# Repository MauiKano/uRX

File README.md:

# uRX Navtex SDR – System Documentation

## 1. Overview
The **uRX** is a high-performance Software Defined Radio (SDR) receiver, specifically optimized for **Navtex** transmissions (518 kHz / 490 kHz). It combines the processing power of the **ESP32-S3** with a precision **Tayloe Mixer** and the versatility of the **Si4732** radio chip.

This project is licensed under the **GNU General Public License v3.0 (GPL-3.0)**.

---

## 2. Technical Hardware Specification

### RF Frontend & Antenna Management
*   **Resonant Ferrite Rod Antenna:** Tuned as a high-Q circuit for the target frequencies.
*   **Signal Splitting:** The antenna signal is buffered and isolated via an **OPA2211** operational amplifier.
*   **Parallel Architecture:** The OPA2211 output simultaneously feeds the **Tayloe Mixer (CBT3253)** for SDR decoding and the **AM antenna input of the Si4732** for parallel monitoring.
*   **ATS-Mini Heritage:** The tuner section for the Si4732 implements the proven circuit design of the **ATS-Mini**, including an optimized FM input network (180nH / 18pF).

### Signal Processing (SDR & Audio)
*   **Dual-Channel Digitization:** A **PCM1808 24-bit ADC** handles the conversion.
    *   **Channel 1 (I/Q SDR):** Differential I/Q signals from the Tayloe Mixer are amplified via an **LM4562** instrumentation stage.
    *   **Channel 2 (Si4732 Audio):** The analog audio output of the Si4732 is routed to the second ADC channel for digital post-processing.
*   **I2S Integration:** Data is streamed via I2S to the ESP32-S3 for real-time decoding and noise reduction.
*   **Audio Output:** A **PAM8406** power amplifier drives the speaker. A dedicated PDM/PWM output provides audio tones for Navtex monitoring.

### Dual Display Architecture
The uRX features a unique dual-display system for maximum utility:
*   **4.2" E-Ink Display:** For low-power, high-contrast viewing of decoded Navtex text messages.
*   **1.9" TFT Display:** For real-time tuning, spectrum visualization, and system menus.

---

## 3. ESP32-S3 GPIO Assignment (WROOM-2 N16)
*Note: Optimized for the N16 (non-PSRAM) variant to ensure all GPIOs are available for peripherals.*

| Function | GPIO | Module Pin | Details |
| :--- | :--- | :--- | :--- |
| **I2C SDA** | 18 | 11 | Si4732, Si5351 (4.7k Pull-up) |
| **I2C SCL** | 03 | 15 | Si4732, Si5351 (4.7k Pull-up) |
| **SPI MOSI** | 01 | 39 | Shared Data (MOSI) |
| **SPI SCLK** | 02 | 38 | Shared Clock (SCLK) |
| **E-INK CS** | 04 | 08 | E-Ink Chip Select |
| **E-INK DC** | 05 | 09 | E-Ink Data/Command |
| **E-INK RST** | 06 | 10 | E-Ink Reset |
| **TFT CS** | 42 | 33 | TFT Chip Select |
| **TFT DC** | 44 | 37 | TFT Data/Command |
| **TFT RST** | 43 | 36 | TFT Reset |
| **I2S_DATA** | 13 | 21 | From PCM1808 ADC |
| **I2S_BCK** | 12 | 20 | Bit Clock (ADC) |
| **I2S_WS** | 11 | 19 | Word Select (ADC) |
| **GPS TX** | 16 | 09 | Data from GPS |
| **GPS RX** | 17 | 10 | Data to GPS |
| **GPS Power** | 15 | 28 | Controls BC847 (GND-Switch) |
| **Audio Out** | 10 | 18 | PDM/PWM Navtex Tones |
| **Encoder A/B**| 38/39| 31/32 | Rotary Encoder Phases |
| **Encoder SW** | 40 | 33 | Encoder Push-Switch |

---

## 4. Installation & Setup
1.  **Environment:** [PlatformIO](https://platformio.org) is recommended.
2.  **Configuration:** Hardware pins are defined in `include/config.h`. 
3.  **Libraries:** GxEPD2, TFT_eSPI, PU2CLR Si4735, Etherkit Si5351, TinyGPS++.
4.  **Flash:** Ensure `ARDUINO_USB_CDC_ON_BOOT=1` is set in `platformio.ini` for native USB programming.

---

## 5. Power & Safety
The system is powered by a **2S LiPo battery (8.4V)** charged via USB-C using the **IP2326**. Ferrite beads and L-C star-filtering are used to protect the sensitive RF stages from switching noise.

**Disclaimer:** This is an experimental open-source project. Handle LiPo batteries with care.

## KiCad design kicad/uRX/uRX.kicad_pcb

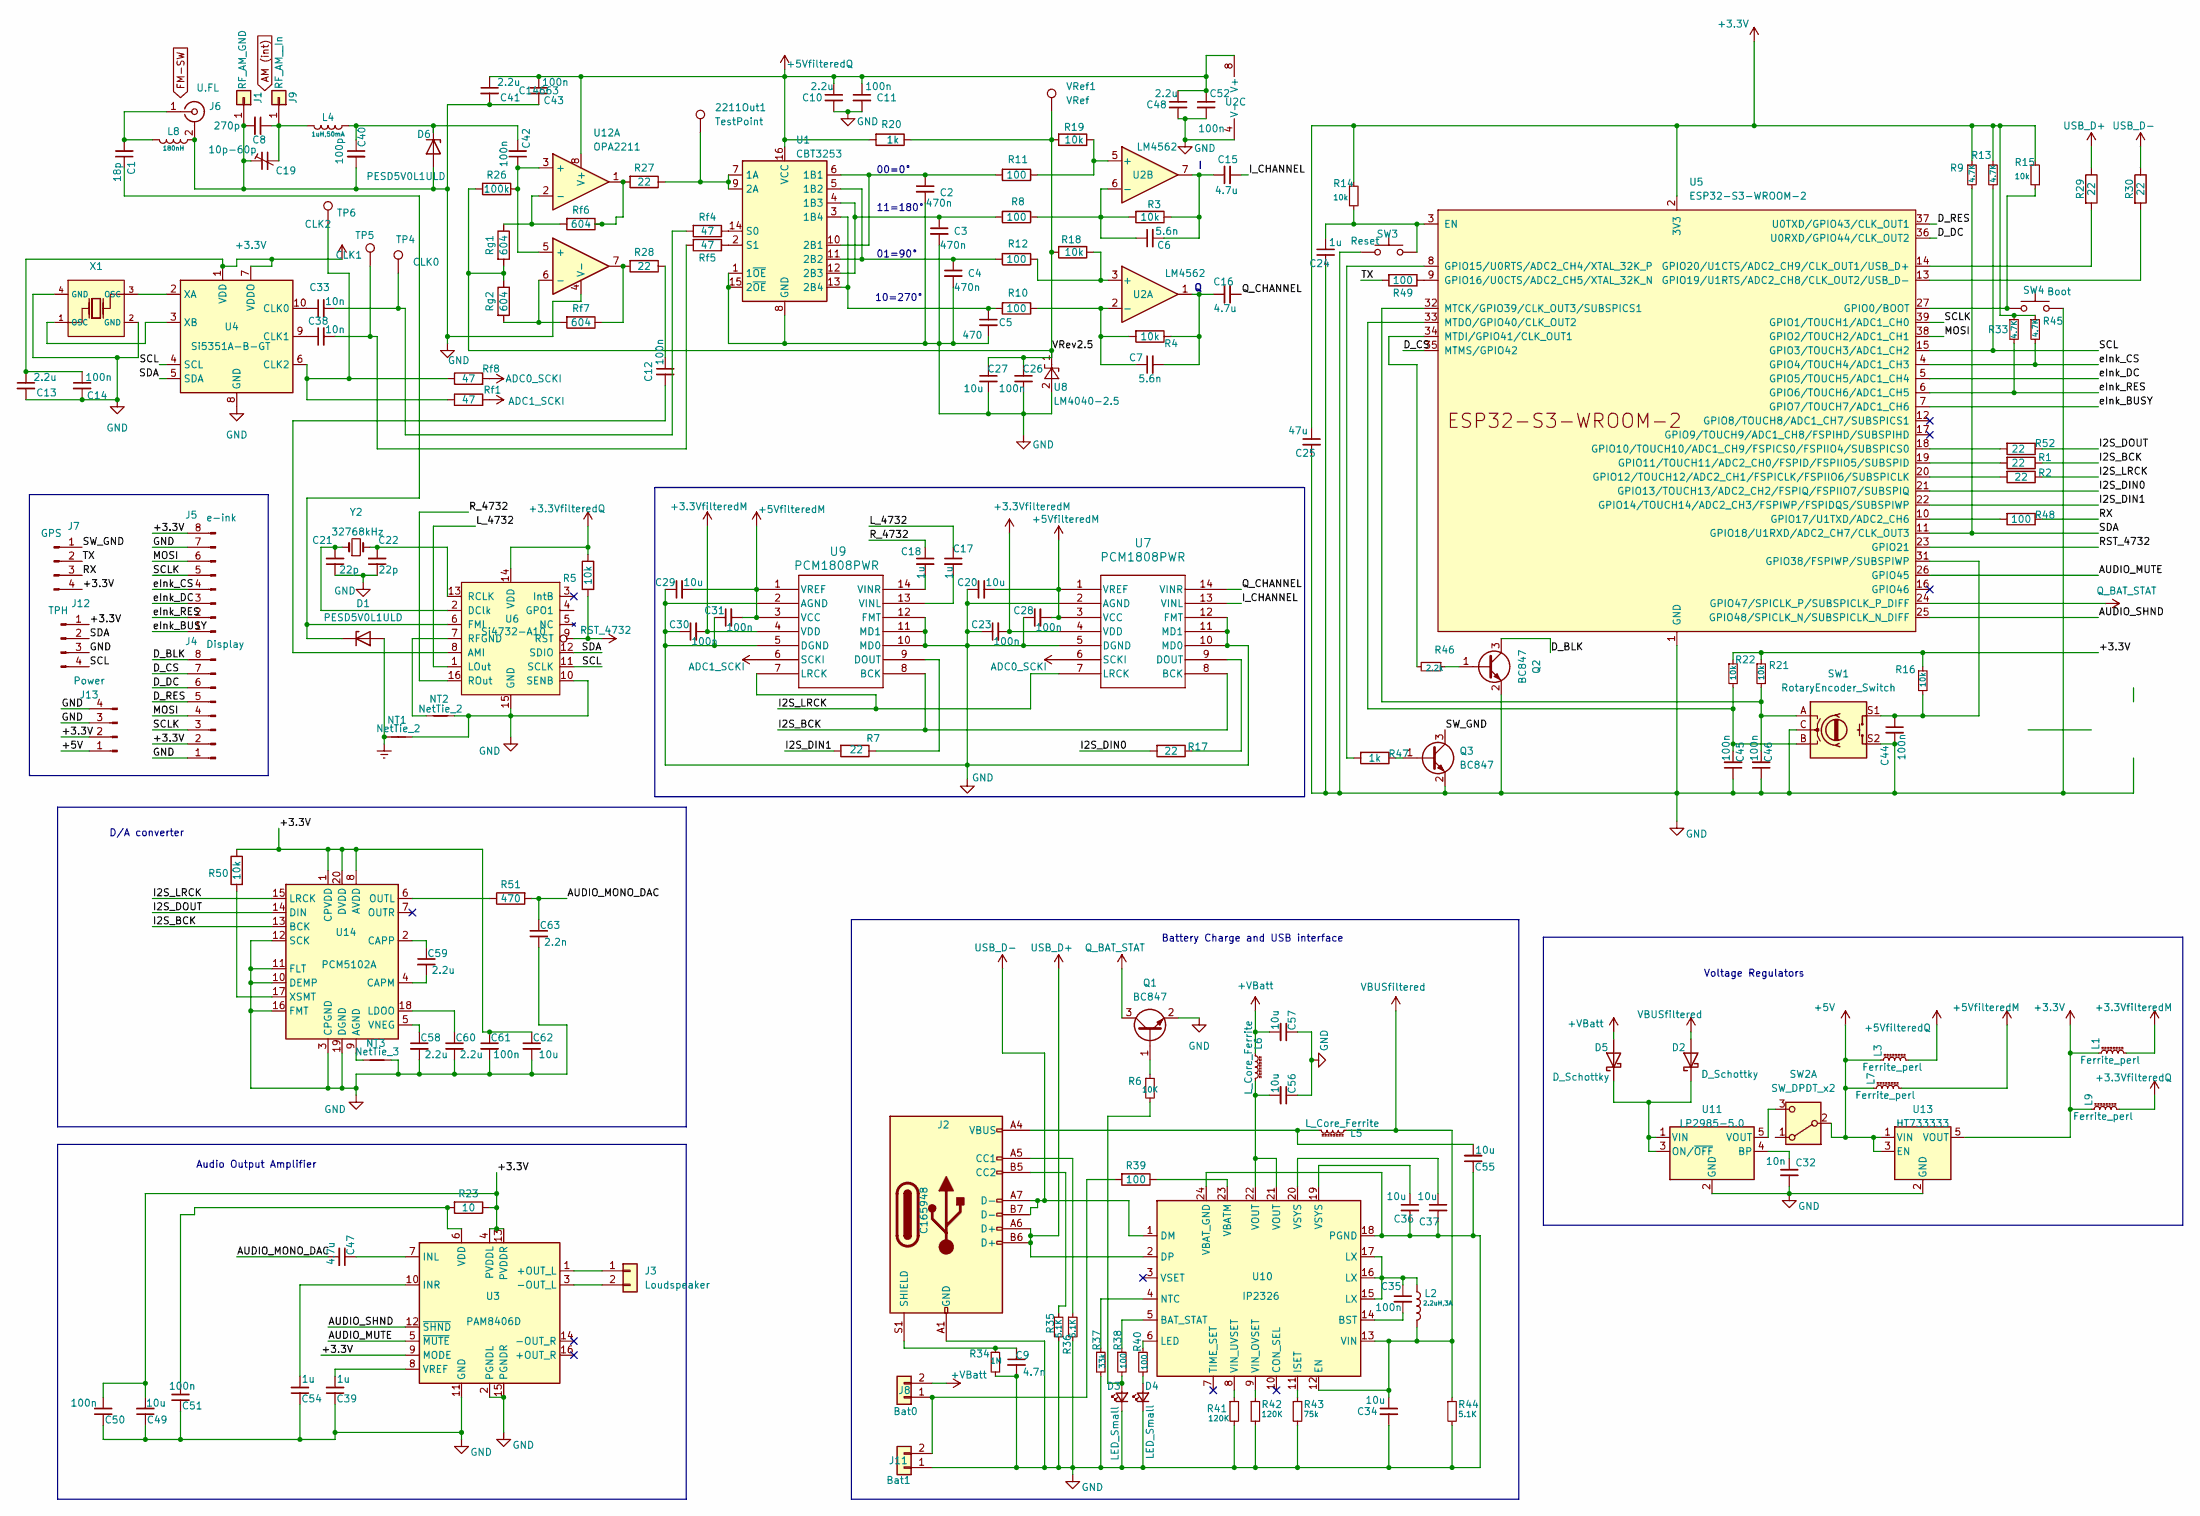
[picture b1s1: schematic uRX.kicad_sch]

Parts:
2211Out1: TestPoint; TestPoint_THTPad_1.0x1.0mm_Drill0.5mm
C1: 18p; C_0603_1608Metric
C2, C3, C4: 470n; C_0603_1608Metric
C5: 470; C_0603_1608Metric
C6, C7: 5.6n; C_0603_1608Metric
C8: 270p; C_0603_1608Metric
C9: 4.7n; C_0603_1608Metric
C10, C13, C41, C48, C58, C59, C60: 2.2u; C_0603_1608Metric
C11, C12, C14, C23, C26, C28, C30, C31, C35, C42, C43, C44, C45, C46, C50, C51, C52, C61: 100n; C_0603_1608Metric
C15, C16, C47: 4.7u; C_0603_1608Metric
C17, C18, C24, C39, C54: 1u; C_0603_1608Metric
C19: 10p-60p; C_Trimmer_Murata_TZC3
C20, C27, C29, C36, C37, C49, C62: 10u; C_0603_1608Metric
C21, C22: 22p; C_0603_1608Metric
C25: 47u; C_0603_1608Metric
C32, C33, C38: 10n; C_0603_1608Metric
C34, C55, C56, C57: 10u; C_0805_2012Metric
C40: 100p; C_0603_1608Metric
C63: 2.2n; C_0603_1608Metric
D1, D6: PESD5V0L1ULD; D_SOD-882D
D2, D5: D_Schottky; D_SOD-123
D3, D4: LED_Small; LED_0603_1608Metric
J1: RF_AM_GND; Pin_D0.9mm_L10.0mm_W2.4mm_FlatFork
J2: C165948; USB_C_Receptacle_GCT_USB4085
J3: Loudspeaker; JST_PH_B2B-PH-K_1x02_P2.00mm_Vertical
J4: Display; PinHeader_1x08_P2.54mm_Vertical
J5: e-ink; PinHeader_1x08_P1.27mm_Horizontal
J6: U.FL; SMA_Molex_73251-1153_EdgeMount_Horizontal; LCSC C5137195
J7: GPS; PinHeader_1x04_P2.54mm_Vertical
J8: Bat0; JST_PH_B2B-PH-K_1x02_P2.00mm_Vertical
J9: RF_AM__In; Pin_D0.9mm_L10.0mm_W2.4mm_FlatFork
J11: Bat1; JST_PH_B2B-PH-K_1x02_P2.00mm_Vertical
J12: TPH; PinHeader_1x04_P2.54mm_Vertical
J13: Power; PinHeader_1x04_P2.54mm_Vertical
L1, L3, L7, L9: Ferrite_perl; L_0603_1608Metric
L2: 2.2uH,3A; L_Taiyo-Yuden_NR-40xx; Tolerance ±10%; Part NRS5024T2R2NMGJ; LCSC C222926
L4: 1uH,50mA; L_0805; Tolerance ±10%; Part SDFL2012Q1R0KTF; LCSC C1042
L5, L6: L_Core_Ferrite; L_Taiyo-Yuden_NR-40xx
L8: 180nH; L_0805; Tolerance ±10%; Part SDFL2012Q1R0KTF; LCSC C1042
NT1, NT2: NetTie_2; NetTie-2_SMD_Pad0.5mm
NT3: NetTie_3; NetTie-2_SMD_Pad0.5mm
Q1, Q2, Q3: BC847; SOT-23
R1, R2, R7, R17, R27, R28, R29, R30, R52: 22; R_0603_1608Metric
R3, R4, R5, R14, R15, R16, R18, R19, R21, R22, R50: 10k; R_0603_1608Metric
R6: 10K; R_0603_1608Metric
R8, R10, R11, R12, R38, R39, R40, R48, R49: 100; R_0603_1608Metric
R9, R13, R33, R45: 4.7K; R_0603_1608Metric
R20, R47: 1k; R_0603_1608Metric
R23: 10; R_0603_1608Metric
R26: 100k; R_0603_1608Metric
R34: 1M; R_0603_1608Metric
R35, R36, R44: 5.1K; R_0603_1608Metric
R37: 33k; R_0603_1608Metric
R41, R42: 120K; R_0603_1608Metric
R43: 75k; R_0603_1608Metric
R46: 2.2k; R_0603_1608Metric
R51: 470; R_0603_1608Metric
Rf1, Rf4, Rf5, Rf8: 47; R_0603_1608Metric
Rf6, Rf7: 604; R_0603_1608Metric
Rg1, Rg2: 604; R_0603_1608Metric
SW1: RotaryEncoder_Switch; RotaryEncoder_Alps_EC11E-Switch_Vertical_H20mm
SW2: SW_DPDT_x2; SW_SPDT_PCM12
SW3: Reset; SW_SPST_B3U-1000P
SW4: Boot; SW_SPST_B3U-1000P
TP4: CLK0; TestPoint_THTPad_1.0x1.0mm_Drill0.5mm
TP5: CLK1; TestPoint_THTPad_1.0x1.0mm_Drill0.5mm
TP6: CLK2; TestPoint_THTPad_1.0x1.0mm_Drill0.5mm
U1: CBT3253; SO-16_3.9x9.9mm_P1.27mm
U2: LM4562; SOIC-8_3.9x4.9mm_P1.27mm
U3: PAM8406D; SOIC-16_3.9x9.9mm_P1.27mm
U4: Si5351A-B-GT; MSOP-10_3x3mm_P0.5mm
U5: ESP32-S3-WROOM-2
U6: Si4732-A10; SSOP-16_3.9x4.9mm_P0.635mm
U7, U9: PCM1808PWR; TSSOP-14_4.4x5mm_P0.65mm
U8: LM4040-2.5; SOT-23-3
U10: IP2326; QFN-24-1EP_4x4mm_P0.5mm_EP2.7x2.7mm
U11: LP2985-5.0; SOT-23-5
U12: OPA2211; SOIC-8_3.9x4.9mm_P1.27mm
U13: HT733333; SOT-23-5
U14: PCM5102A; TSSOP-20_4.4x6.5mm_P0.65mm
VRef1: VRef; TestPoint_THTPad_1.0x1.0mm_Drill0.5mm
X1: X322525MOB4SI; Crystal_SMD_3225-4Pin_3.2x2.5mm; Frequency Tolerance ±10ppm; Part X322525MOB4SI; LCSC C9006
Y2: 32768kHz; Crystal_SMD_3215-2Pin_3.2x1.5mm

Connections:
+3.3V: C13.1, C14.1, C25.1, C49.2, C50.2, C61.1, C62.1, J4.2, J5.8, J7.4, J12.1, J13.2, L1.1, L9.1, R9.1, R13.1, R14.1, R15.1, R16.1, R21.1, R22.1, R23.1, R33.1, R45.1, R50.1, U3.4 (PVDDL), U3.9 (MODE), U3.13 (PVDDR), U4.1 (VDD), U4.7 (VDDO), U5.2 (3V3), U13.5 (VOUT), U14.1 (CPVDD), U14.8 (AVDD), U14.20 (DVDD)
+3.3VfilteredM: C23.2, C30.2, L1.2, U7.4 (VDD), U9.4 (VDD)
+3.3VfilteredQ: L9.2, R5.1, U6.14 (VDD)
+5V: J13.1, L3.1, L7.1, SW2.2 (B), U13.1 (VIN), U13.3 (EN)
+5VfilteredM: C20.2, C28.2, C29.2, C31.2, L7.2, U7.1 (VREF), U7.3 (VCC), U9.1 (VREF), U9.3 (VCC)
+5VfilteredQ: C10.1, C11.1, C41.1, C43.1, C48.1, C52.1, L3.2, R20.2, U1.16 (VCC), U2.8 (V+), U12.8 (V+)
+VBatt: C57.2, D5.2 (A), J8.2, L6.1
/AUDIO_MONO_DAC: C47.2, C63.1, R51.2
/AUDIO_MUTE: U3.5 (~MUTE), U5.26 (GPIO45)
/AUDIO_SHND: U3.12 (~SHND), U5.25 (GPIO48/SPICLK_N/SUBSPICLK_N_DIFF)
/D_BLK: J4.8, Q2.3 (C)
/D_CS: J4.7, U5.35 (MTMS/GPIO42)
/D_DC: J4.6, U5.36 (U0RXD/GPIO44/CLK_OUT2)
/D_RES: J4.5, U5.37 (U0TXD/GPIO43/CLK_OUT1)
/I2S_BCK: R1.1, U7.8 (BCK), U9.8 (BCK), U14.13 (BCK)
/I2S_DIN0: R17.2, U5.21 (GPIO13/TOUCH13/ADC2_CH2/FSPIQ/FSPIIO7/S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)
/I2S_DIN1: R7.2, U5.22 (GPIO14/TOUCH14/ADC2_CH3/FSPIWP/FSPIDQS/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)
/I2S_DOUT: R52.1, U14.14 (DIN)
/I2S_LRCK: R2.1, U7.7 (LRCK), U9.7 (LRCK), U14.15 (LRCK)
/I_CHANNEL: C15.2, U7.13 (VINL)
/L_4732: C17.1, U6.1 (LOut)
/MOSI: J4.4, J5.6, U5.38 (GPIO2/TOUCH2/ADC1_CH1)
/Q_CHANNEL: C16.2, U7.14 (VINR)
/RX: J7.3, R48.1
/R_4732: C18.1, U6.16 (ROut)
/SCL: J12.4, R13.2, U4.4 (SCL), U5.15 (GPIO3/TOUCH3/ADC1_CH2), U6.11 (SCLK)
/SCLK: J4.3, J5.5, U5.39 (GPIO1/TOUCH1/ADC1_CH0)
/SDA: J12.2, R9.2, U4.5 (SDA), U5.11 (GPIO18/U1RXD/ADC2_CH7/CLK_OUT3), U6.12 (SDIO)
/SW_GND: J7.1, Q3.3 (C)
/TX: J7.2, R49.2
/VRev2.5: C26.1, C27.1, R18.2, R19.2, R20.1, R26.2, Rg1.2, Rg2.1, U8.1 (K), VRef1.1
/eInk_BUSY: J5.1, U5.7 (GPIO7/TOUCH7/ADC1_CH6)
/eInk_CS: J5.4, R45.2, U5.4 (GPIO4/TOUCH4/ADC1_CH3)
/eInk_DC: J5.3, U5.5 (GPIO5/TOUCH5/ADC1_CH4)
/eInk_RES: J5.2, R33.2, U5.6 (GPIO6/TOUCH6/ADC1_CH5)
ADC0_SCKI: Rf8.2, U7.6 (SCKI)
ADC1_SCKI: Rf1.2, U9.6 (SCKI)
Earth: D1.2 (A), NT1.1
unnamed: C12.1, R28.1
unnamed: C6.2, C15.1, R3.1, U2.7
unnamed: C7.2, C16.1, R4.1, U2.1
unnamed: C33.2, Rf4.2, TP4.1
unnamed: C35.1, L2.1, U10.15 (LX), U10.16 (LX), U10.17 (LX)
unnamed: C36.1, U10.19 (VSYS)
unnamed: C37.1, U10.20 (VSYS)
unnamed: C38.2, Rf5.2, TP5.1
unnamed: C42.1, R26.1, U12.3 (+), U12.5 (+)
unnamed: C55.2, J2.A4 (VBUS), J2.A9 (VBUS), J2.B4 (VBUS), J2.B9 (VBUS), L5.2
unnamed: C56.2, L6.2, U10.21 (VOUT), U10.22 (VOUT)
unnamed: C1.1, D1.1 (K), U6.6 (FMI)
unnamed: D2.1 (K), D5.1 (K), U11.1 (VIN), U11.3 (ON/~OFF)
unnamed: D3.2 (A), R6.2, R38.2
unnamed: D4.2 (A), R40.2
unnamed: C40.1, C42.2, D6.1 (K), L4.1
unnamed: J2.A5 (CC1), R36.1
unnamed: J2.B5 (CC2), R35.1
unnamed: C9.1, J2.S1 (SHIELD), R34.1
unnamed: J3.1, U3.1 (+OUT_L)
unnamed: J3.2, U3.3 (-OUT_L)
unnamed: C1.2, J6.1 (In), L8.2
unnamed: C8.1, C19.2, J9.1, L4.2
unnamed: J8.1, J11.2, R39.2
unnamed: Q1.1 (B), R6.1
unnamed: Q2.1 (B), R46.1
unnamed: Q3.1 (B), R47.1
unnamed: R27.2, Rf6.1, U12.1
unnamed: R28.2, Rf7.1, U12.7
unnamed: Rf6.2, Rg1.1, U12.2 (-)
unnamed: Rf7.2, Rg2.2, U12.6 (-)
unnamed: SW2.3 (C), U11.5 (VOUT)
unnamed: 2211Out1.1, R27.1, U1.7 (1A), U1.9 (2A)
unnamed: C2.1, R11.2, U1.6 (1B1), U1.10 (2B1)
unnamed: C4.1, R12.2, U1.5 (1B2), U1.11 (2B2)
unnamed: C3.1, R8.2, U1.4 (1B3), U1.12 (2B3)
unnamed: C5.1, R10.2, U1.3 (1B4), U1.13 (2B4)
unnamed: Rf4.1, U1.14 (S0)
unnamed: Rf5.1, U1.2 (S1)
unnamed: R12.1, R18.1, U2.3 (+)
unnamed: C7.1, R4.2, R10.1, U2.2 (-)
unnamed: R11.1, R19.1, U2.5 (+)
unnamed: C6.1, R3.2, R8.1, U2.6 (-)
unnamed: C47.1, U3.7 (INL)
unnamed: C54.2, U3.10 (INR)
unnamed: C51.2, R23.2, U3.6 (VDD)
unnamed: C39.2, U3.8 (VREF)
unnamed: C33.1, U4.10 (CLK0)
unnamed: C38.1, U4.9 (CLK1)
unnamed: Rf1.1, Rf8.1, TP6.1, U4.6 (CLK2)
unnamed: U4.2 (XA), X1.3 (OSC)
unnamed: U4.3 (XB), X1.1 (OSC)
unnamed: C24.1, R14.2, SW3.2, U5.3 (EN)
unnamed: R15.2, SW4.1, U5.27 (GPIO0/BOOT)
unnamed: R52.2, U5.18 (GPIO10/TOUCH10/ADC1_CH9/FSPICS0/FSPIIO4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)
unnamed: R1.2, U5.19 (GPIO11/TOUCH11/ADC2_CH0/FSPID/FSPIIO5/S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)
unnamed: R2.2, U5.20 (GPIO12/TOUCH12/ADC2_CH1/FSPICLK/FSPIIO6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)
unnamed: R47.2, U5.8 (GPIO15/U0RTS/ADC2_CH4/XTAL_32K_P)
unnamed: R49.1, U5.9 (GPIO16/U0CTS/ADC2_CH5/XTAL_32K_N)
unnamed: R48.2, U5.10 (GPIO17/U1TXD/ADC2_CH6)
unnamed: R30.2, U5.13 (GPIO19/U1RTS/ADC2_CH8/CLK_OUT2/USB_D-)
unnamed: R29.2, U5.14 (GPIO20/U1CTS/ADC2_CH9/CLK_OUT1/USB_D+)
unnamed: C44.1, R16.2, SW1.S1, U5.31 (GPIO38/FSPIWP/SUBSPIWP)
unnamed: C46.2, R21.2, SW1.A, U5.32 (MTCK/GPIO39/CLK_OUT3/SUBSPICS1)
unnamed: R46.2, U5.34 (MTDI/GPIO41/CLK_OUT1)
unnamed: C45.2, R22.2, SW1.B, U5.33 (MTDO/GPIO40/CLK_OUT2)
unnamed: C12.2, U6.8 (AMI)
unnamed: C21.2, U6.2 (DClk), Y2.1
unnamed: C22.2, U6.13 (RCLK), Y2.2
unnamed: NT2.1, U6.7 (RFGND)
unnamed: R17.1, U7.9 (DOUT)
unnamed: R7.1, U9.9 (DOUT)
unnamed: C17.2, U9.13 (VINL)
unnamed: C18.2, U9.14 (VINR)
unnamed: R38.1, U10.5 (BAT_STAT)
unnamed: C35.2, U10.14 (BST)
unnamed: R43.1, U10.11 (ISET)
unnamed: R40.1, U10.6 (LED)
unnamed: R37.1, U10.4 (NTC)
unnamed: R39.1, U10.23 (VBATM)
unnamed: R42.1, U10.9 (VIN_OVSET)
unnamed: C32.1, U11.4 (BP)
unnamed: NT3.1, U14.9 (AGND)
unnamed: C59.2, U14.4 (CAPM)
unnamed: C59.1, U14.2 (CAPP)
unnamed: C60.1, U14.18 (LDOO)
unnamed: R51.1, U14.6 (OUTL)
unnamed: C58.1, U14.5 (VNEG)
unnamed: R50.2, U14.17 (XSMT)
Q_BAT_STAT: Q1.3 (C), U5.24 (GPIO47/SPICLK_P/SUBSPICLK_P_DIFF)
RST_4732: R5.2, U5.23 (GPIO21), U6.9 (RST)
USB_D+: J2.A6 (D+), J2.B6 (D+), R29.1, U10.2 (DP)
USB_D-: J2.A7 (D-), J2.B7 (D-), R30.1, U10.1 (DM)
VBUSfiltered: C34.1, D2.2 (A), L2.2, L5.1, R44.1, U10.12 (EN), U10.13 (VIN)

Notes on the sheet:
00=0°
Audio Output Amplifier
Voltage Regulators
D/A converter
10=270°
11=180°
01=90°
Battery Charge and USB interface

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
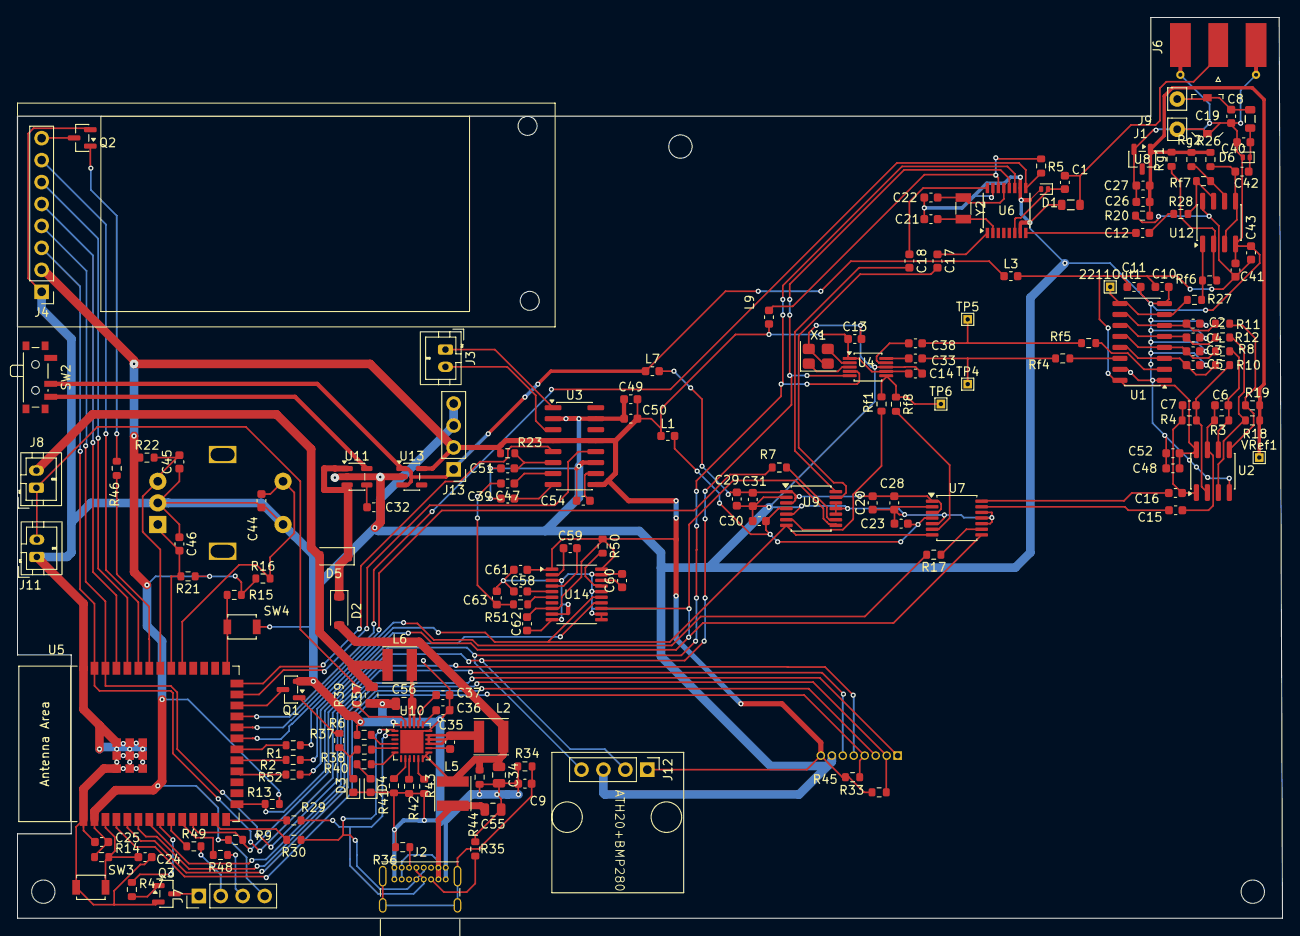
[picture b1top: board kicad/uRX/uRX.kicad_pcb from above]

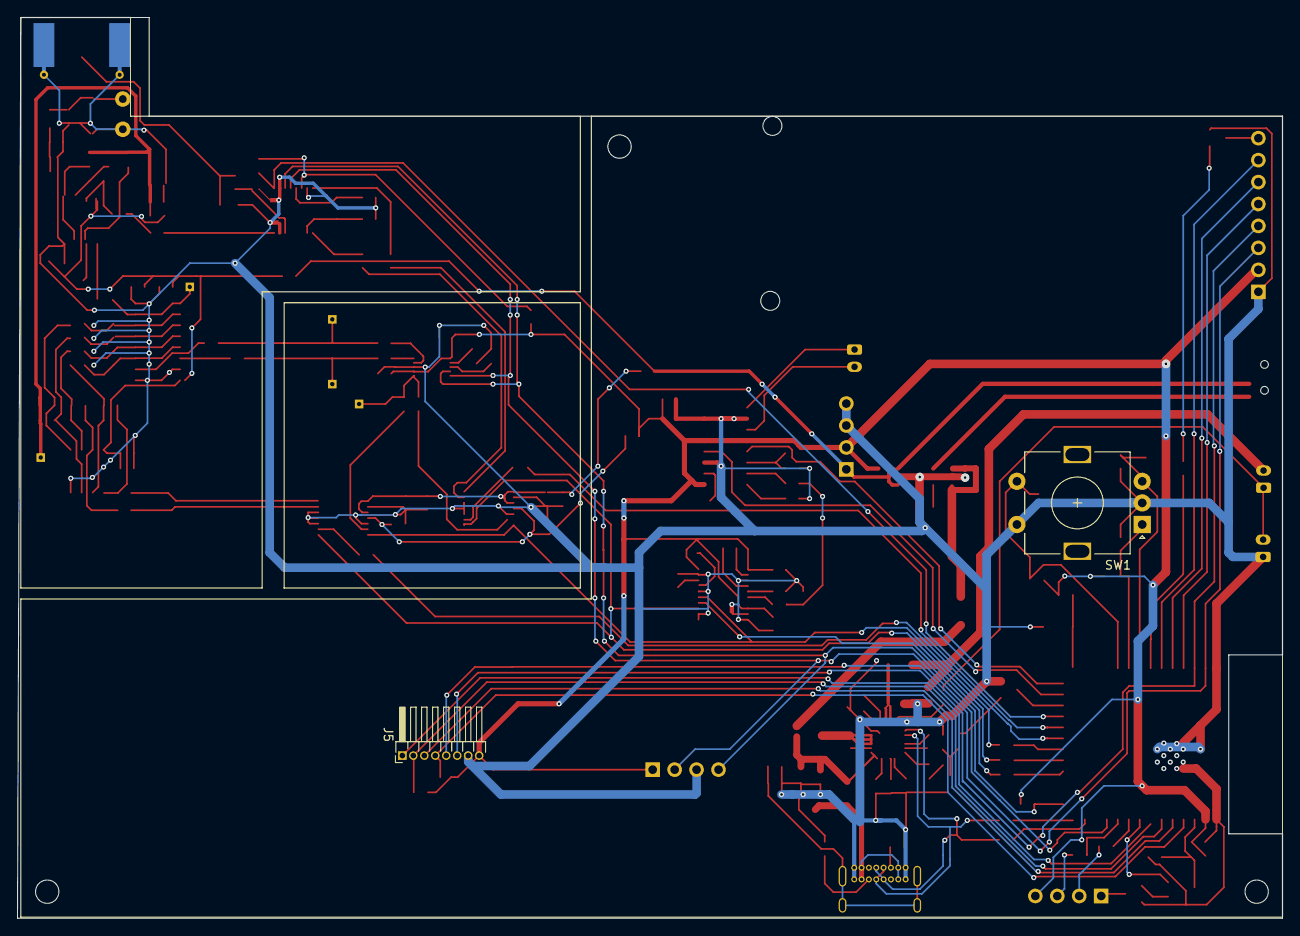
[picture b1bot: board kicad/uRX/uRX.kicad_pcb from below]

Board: 2 copper layers, 146.4 x 104.3 mm, 180 parts (2 on the bottom side), 134 nets.

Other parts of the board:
M2, M2#2, M2#3, M2#4: MountingHole_2.2mm_M2_DIN965

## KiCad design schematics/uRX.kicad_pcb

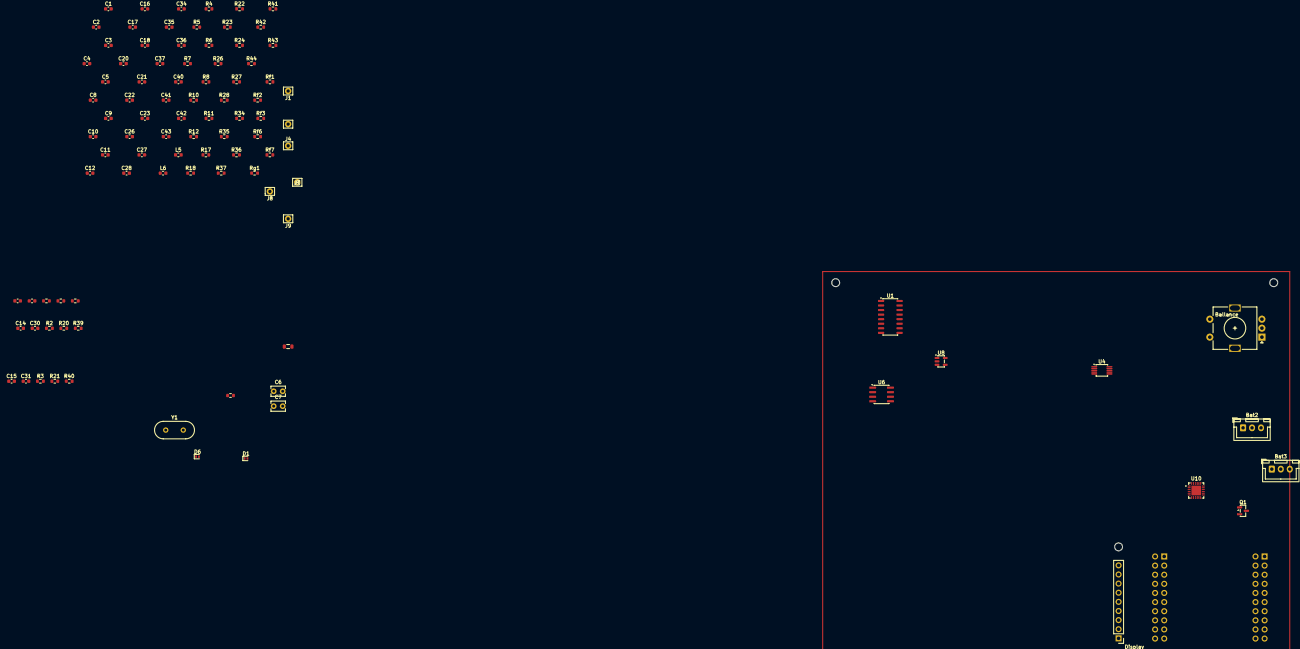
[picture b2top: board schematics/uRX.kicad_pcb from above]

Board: 2 copper layers, 103 parts (0 on the bottom side), 59 nets, no tracks yet.

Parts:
Bat2, Bat3: JST-XH; JST_XH_B3B-XH-A_1x03_P2.50mm_Vertical
C1, C40: 100p; C_0603_1608Metric
C2, C3, C4, C5: 220n; C_0603_1608Metric
C6, C7: 1.2n; C_Disc_D3.8mm_W2.6mm_P2.50mm
C8: 270p; C_0603_1608Metric
C9: 4.7n; C_0603_1608Metric
C10, C41: 2.2u; C_0603_1608Metric
C11, C12, C23, C26, C28, C30, C31, C35, C42, C43: 100n; C_0603_1608Metric
C13, C14: 2..20p; C_0603_1608Metric
C15, C16, C17, C18: 4.7u; C_0603_1608Metric
C20, C27, C29, C34, C36, C37: 10u; C_0603_1608Metric
C21, C22: 22p; C_0603_1608Metric
D1, D6: PESD5V0L1ULD; D_SOD-882D
Display: PinHeader_1x09_P2.54mm_Vertical
J1: RF_GMD; Pin_D0.9mm_L10.0mm_W2.4mm_FlatFork
J4: +5Vfiltered; Pin_D0.9mm_L10.0mm_W2.4mm_FlatFork
J5: +5V; Pin_D0.9mm_L10.0mm_W2.4mm_FlatFork
J7: +3.3Vfiltered; Pin_D0.9mm_L10.0mm_W2.4mm_FlatFork
J8, J9: RF_In; Pin_D0.9mm_L10.0mm_W2.4mm_FlatFork
L4: 1uH,50mA; L_0805
L5, L6: Ferrite_perl; L_0603_1608Metric
M2, M2#2, M2#3, M2#4, M2#5, M2#6: MountingHole_2.2mm_M2_DIN965
Q1: BC847; SOT-23
R1, R2, R21, R22, R23, R24, R27, R28: 22; R_0603_1608Metric
R3, R4, R18, R19: 47k; R_0603_1608Metric
R5: 10k; R_0603_1608Metric
R6: 10K; R_0603_1608Metric
R7, R17: 4.7kΩ; R_0603_1608Metric
R8, R10, R11, R12, R20: 1k; R_0603_1608Metric
R26: 100k; R_0603_1608Metric
R34: 1M; R_0603_1608Metric
R35, R36, R44: 5.1K; R_0603_1608Metric
R37: 33k; R_0603_1608Metric
R38, R39, R40: 100; R_0603_1608Metric
R41, R42: 120K; R_0603_1608Metric
R43: 75k; R_0603_1608Metric
Rf1: 33; R_0603_1608Metric
Rf2, Rf3: 47; R_0603_1608Metric
Rf6, Rf7: 604; R_0603_1608Metric
Rg1, Rg2: 604; R_0603_1608Metric
U1: CBT3253; SO-16_3.9x9.9mm_P1.27mm
U4: Si5351A-B-GT; MSOP-10_3x3mm_P0.5mm
U6: Si4732-A10; SOIC-8_3.9x4.9mm_P1.27mm
U8: LM4040-2.5; SOT-23-5
U10: IP2326; QFN-24-1EP_4x4mm_P0.5mm_EP2.7x2.7mm
Y1: 25MHz; Crystal_HC49-U_Vertical

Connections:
+3.3V: L5.1, R7.1, R17.1, U4.1 (VDD), U4.7 (VDDO)
+3.3Vfiltered: C23.2, C30.2, R5.1
+5V: Bat2.3, Bat3.3, L6.1, U10.21 (VOUT), U10.22 (VOUT)
+5Vfiltered: C10.1, C11.1, C20.2, C28.2, C29.2, C31.2, C41.1, C43.1, R20.2, U1.16 (VCC)
/SCL: R17.2, U4.4 (SCL)
/SDA: R7.2, U4.5 (SDA)
/VRev2.5: C26.1, C27.1, R18.2, R19.2, R20.1, R26.2, Rg1.2, Rg2.1, U8.4 (K)
Earth: D1.2 (A), U6.7 (RFGND)
GND: Bat2.1, Bat3.1, C2.2, C3.2, C4.2, C5.2, C8.2, C9.2, C10.2, C11.2, C13.2, C14.2, C20.1, C21.1, C22.1, C23.1, C26.2, C27.2, C28.1, C29.1, C30.1, C31.1, C34.2, C36.2, C37.2, C40.2, C41.2, C43.2, D6.2 (A), Display.1, J1.1, Q1.2 (E), R34.2, R35.2, R36.2, R37.2, R41.2, R42.2, R43.2, R44.2, U1.1 (1~OE), U1.8 (GND), U1.15 (2~OE), U4.8 (GND), U8.5 (A), U10.18 (PGND), U10.24 (VBAT_GND)
unnamed: Bat2.2, Bat3.2, R39.2
unnamed: C12.1, R28.1
unnamed: C6.2, C15.1, R3.1
unnamed: C7.2, C16.1, R4.1
unnamed: C35.1, U10.16 (LX)
unnamed: C36.1, U10.19 (VSYS)
unnamed: C37.1, U10.20 (VSYS)
unnamed: C42.1, R26.1
unnamed: C1.1, D1.1 (K), U6.6 (FMI)
unnamed: R6.2, R38.2
unnamed: C40.1, C42.2, D6.1 (K), L4.1
unnamed: C9.1, R34.1
unnamed: J4.1, L6.2
unnamed: J7.1, L5.2
unnamed: C1.2, J8.1
unnamed: C8.1, J9.1, L4.2
unnamed: Q1.1 (B), R6.1
unnamed: R27.2, Rf6.1
unnamed: R28.2, Rf7.1
unnamed: Rf6.2, Rg1.1
unnamed: Rf7.2, Rg2.2
unnamed: R27.1, U1.7 (1A), U1.9 (2A)
unnamed: C2.1, R11.2, U1.6 (1B1), U1.10 (2B1)
unnamed: C4.1, R12.2, U1.5 (1B2), U1.11 (2B2)
unnamed: C5.1, R10.2, U1.4 (1B3), U1.12 (2B3)
unnamed: C3.1, R8.2, U1.3 (1B4), U1.13 (2B4)
unnamed: Rf3.1, U1.14 (S0)
unnamed: Rf2.1, U1.2 (S1)
unnamed: R12.1, R18.1
unnamed: C7.1, R4.2, R10.1
unnamed: R11.1, R19.1
unnamed: C6.1, R3.2, R8.1
unnamed: Rf3.2, U4.10 (CLK0)
unnamed: Rf2.2, U4.9 (CLK1)
unnamed: Rf1.2, U4.6 (CLK2)
unnamed: C13.1, U4.2 (XA), Y1.2
unnamed: C14.1, U4.3 (XB), Y1.1
unnamed: C12.2, U6.8 (AMI)
unnamed: C21.2, U6.2 (DClk)
unnamed: C17.2, U6.1 (LOut)
unnamed: R38.1, U10.5 (BAT_STAT)
unnamed: C35.2, U10.14 (BST)
unnamed: C34.1, R44.1, U10.12 (EN), U10.13 (VIN)
unnamed: R41.1, U10.8 (VIN_UVSET), U10.25 (GND)
unnamed: R43.1, U10.11 (ISET)
unnamed: R40.1, U10.6 (LED)
unnamed: U10.15 (LX), U10.17 (LX)
unnamed: R37.1, U10.4 (NTC)
unnamed: R39.1, U10.23 (VBATM)
unnamed: R42.1, U10.9 (VIN_OVSET)

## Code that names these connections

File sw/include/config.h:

#ifndef CONFIG_H
#define CONFIG_H

#include <Arduino.h>

/**
 * uRX Navtex SDR - Global Configuration
 * Optimized for ESP32-S3-WROOM-2 (N16 / Non-PSRAM Variant)
 * License: GPL-3.0
 */

// --- I2C BUS (Radio Chips: Si5351 & Si4732) ---
#define I2C_SDA_PIN      18  // Pin 11 (WROOM-2)
#define I2C_SCL_PIN       3  // Pin 15 (WROOM-2)
#define I2C_FREQ     400000  // 400kHz Fast Mode

#define SI5351_ADDR    0x60
#define SI4732_ADDR    0x11  // SEN Pin to GND

// --- SHARED SPI BUS (MOSI/SCLK for Displays) ---
#define SPI_MOSI_PIN      1  // Pin 39 (WROOM-2) - SDA Label
#define SPI_SCLK_PIN      2  // Pin 38 (WROOM-2) - SCL Label

// --- 4.2" E-INK DISPLAY (WeAct/GxEPD2) ---
#define EINK_CS_PIN       4  // Pin 8  (WROOM-2)
#define EINK_DC_PIN       5  // Pin 9  (WROOM-2)
#define EINK_RST_PIN      6  // Pin 10 (WROOM-2)
#define EINK_BUSY_PIN     7  // Pin 11 (Busy Signal Input)

// --- 1.9" TFT DISPLAY (ST7789) ---
#define TFT_CS_PIN       42  // Pin 33 (WROOM-2)
#define TFT_DC_PIN       44  // Pin 37 (WROOM-2)
#define TFT_RST_PIN      43  // Pin 36 (WROOM-2)
#define TFT_BLK_PIN      21  // Pin 22 (WROOM-2) - Backlight via BC847

// --- I2S FULL-DUPLEX BUS (ADC0, ADC1, DAC) ---
// Shared Clocks
#define I2S_BCK_PIN      12  // Pin 20 (WROOM-2) - Shared Bit Clock
#define I2S_WS_PIN       11  // Pin 19 (WROOM-2) - Shared Word Select
// Data Lines
#define I2S_ADC0_DIN     13  // Pin 21 (WROOM-2) - SDR I/Q Data (ADC0)
#define I2S_ADC1_DIN     14  // Pin 22 (WROOM-2) - Radio Audio (ADC1)
#define I2S_DAC_DOUT     10  // Pin 18 (WROOM-2) - Unified Audio Out (DAC)
#define SAMPLE_RATE   48000

// --- GPS MODULE (JST-SH 1.0mm) ---
#define GPS_TX_PIN       16  // Pin 9  (WROOM-2) - ESP TX -> GPS RX
#define GPS_RX_PIN       17  // Pin 10 (WROOM-2) - ESP RX <- GPS TX
#define GPS_EN_PIN       15  // Pin 28 (WROOM-2) - GND-Switch via BC847
#define GPS_BAUD       9600

// --- USER INPUT (Rotary Encoder) ---
#define ENCODER_A        38  // Pin 31 (WROOM-2)
#define ENCODER_B        39  // Pin 32 (WROOM-2)
#define ENCODER_SW       40  // Pin 33 (WROOM-2)

// --- MISC / POWER ---
#define BAT_STAT_PIN     41  // Pin 34 (WROOM-2) - Charging Status IP2326
#define SI4732_MUTE_PIN  47  // Pin 35 (WROOM-2) - Hardware Mute Control

#endif // CONFIG_H

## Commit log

2026-01-29 schematics finalization
2026-01-30 add usb power
2026-01-31 finalize power circuit
2026-01-31 add power to the rest
2026-01-31 netlist file
2026-01-31 gpio to vbat_stat
2026-02-01 use opa2211 in AM Antenna input
2026-02-02 start pcb
2026-02-03 resolve missing footprints
2026-02-04 add esp32 to pcb
2026-02-05 work on rf frontend and battery charger
2026-02-06 work on rf part pcb
2026-02-07 finalize rf, 4732 and clock
2026-02-07 connect all together, v0
2026-02-08 pcb digital zone
2026-02-08 add audio amp
2026-02-09 split stero-mono
2026-02-09 clean-up pcb
2026-02-09 all lines connected
2026-02-10 work on power lines
2026-02-10 seafile corruption
2026-02-11 correct taylo
2026-02-11 add e-inc wiring
2026-02-11 feels like the schematics/pcb is complete
2026-02-12 correct i2c - mosi/sclk
2026-02-12 cleanup
2026-02-12 add some docu/config.h
2026-02-13 add dac
2026-02-13 esp verify code compiled
2026-02-14 set gnd/vcc lines propperly
2026-02-14 drc run cleanup
